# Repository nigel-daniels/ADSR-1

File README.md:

# Envelope Generator

This design is for an ADSR evvelope generator, it is based on the [Guru Gara Synth 3310 ADSR](https://gurugarasynth.com/products/3310-adsr-envelope-generator-eurorack-pcb-and-front-panel-for-diy-synth) AS3310 based envelope generator as this too uses the AS3310 and it's core. The design then adds in an LED indicator inspired by the [DIYSythMNL ADSR 3310](https://diysynthmnl.github.io/p/as3310-voltage-controlled-adsr/) and a gate trigger button of my own design.

## Calibration
The trim pot is used to fine tune the timing of the AS3310 attack phase, in the data sheet they use a 30K resistor but here we have a 16K resistor and a 20k trim pot. This adjusts the timing and is especially noticable on the attack. You probably want an oscilloscope for this although you can get close enough by ear.

> Nigel Daniels 2026
> https://bleepsnbloops.com
> Released under the CERN Open Hardware Licence Version 2 - Strongly Reciprocal

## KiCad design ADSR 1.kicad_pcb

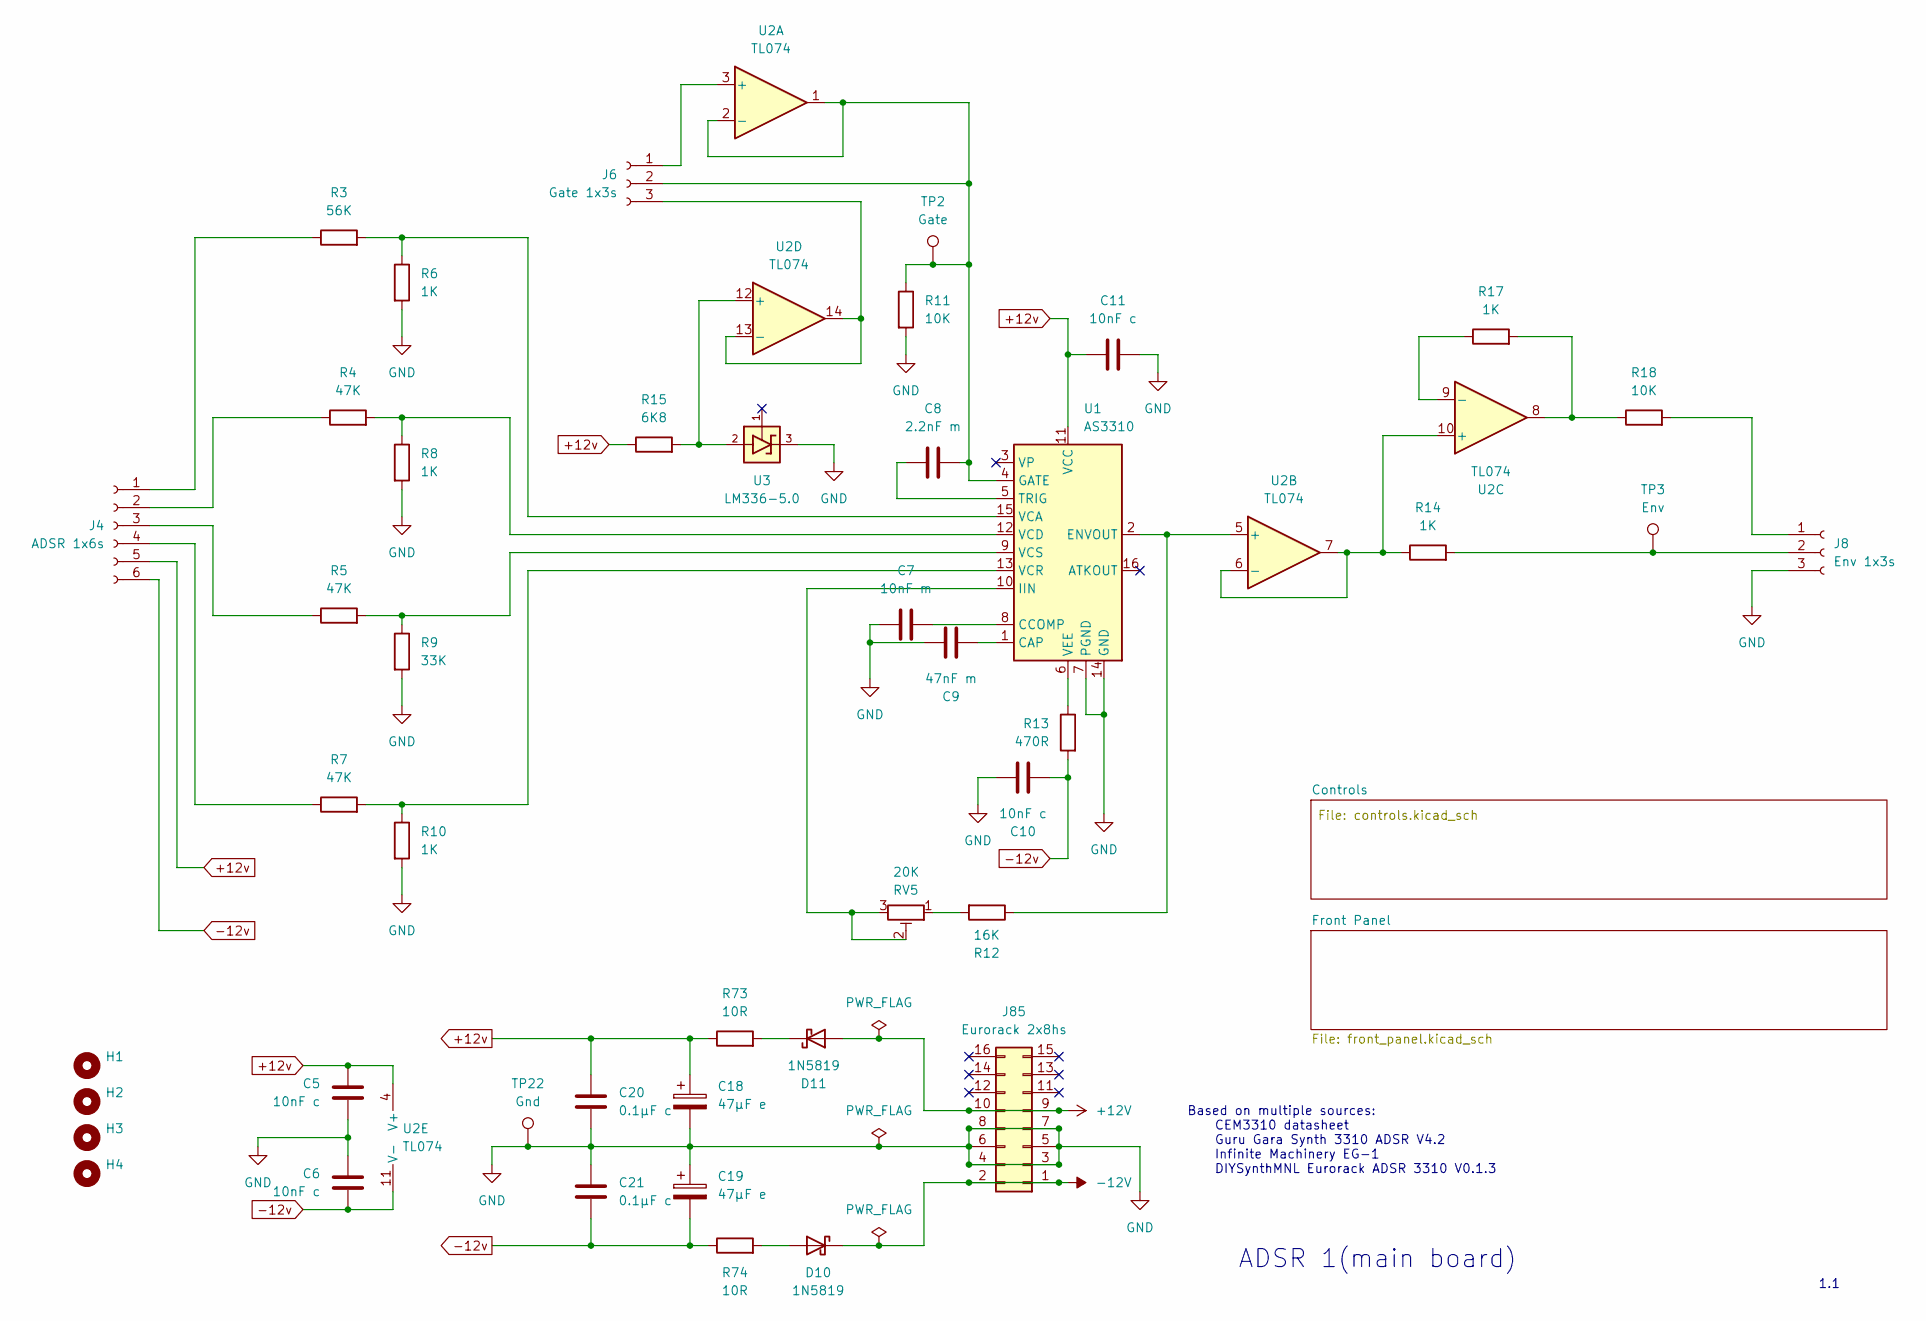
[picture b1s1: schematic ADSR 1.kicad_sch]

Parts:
C5, C6, C10, C11: 10nF c; C_Disc_D4.7mm_W2.5mm_P5.00mm
C7: 10nF m; C_Rect_L7.2mm_W2.5mm_P5.00mm
C8: 2.2nF m; C_Rect_L7.2mm_W2.5mm_P5.00mm
C9: 47nF m; C_Rect_L7.2mm_W2.5mm_P5.00mm
C18, C19: 47μF e; CP_Radial_D5.0mm_P2.50mm
C20, C21: 0.1μF c; C_Disc_D4.7mm_W2.5mm_P5.00mm
D10, D11: 1N5819; D_DO-41_SOD81_P10.16mm_Horizontal
H1, H2, H3, H4: MountingHole_2.7mm_M2.5
J4: ADSR 1x6s; PinSocket_1x06_P2.54mm_Vertical
J6: Gate 1x3s; PinSocket_1x03_P2.54mm_Vertical
J8: Env 1x3s; PinSocket_1x03_P2.54mm_Vertical
J85: Eurorack 2x8hs; IDC-Header_2x08_P2.54mm_Vertical
R3: 56K; R_Axial_DIN0204_L3.6mm_D1.6mm_P2.54mm_Vertical
R4, R5: 47K; R_Axial_DIN0204_L3.6mm_D1.6mm_P2.54mm_Vertical
R6, R8, R10, R17: 1K; R_Axial_DIN0204_L3.6mm_D1.6mm_P2.54mm_Vertical
R7: 47K; R_Axial_DIN0204_L3.6mm_D1.6mm_P7.62mm_Horizontal
R9: 33K; R_Axial_DIN0204_L3.6mm_D1.6mm_P2.54mm_Vertical
R11, R18: 10K; R_Axial_DIN0204_L3.6mm_D1.6mm_P7.62mm_Horizontal
R12: 16K; R_Axial_DIN0204_L3.6mm_D1.6mm_P7.62mm_Horizontal
R13: 470R; R_Axial_DIN0204_L3.6mm_D1.6mm_P7.62mm_Horizontal
R14: 1K; R_Axial_DIN0204_L3.6mm_D1.6mm_P7.62mm_Horizontal
R15: 6K8; R_Axial_DIN0204_L3.6mm_D1.6mm_P7.62mm_Horizontal
R73, R74: 10R; R_Axial_DIN0204_L3.6mm_D1.6mm_P2.54mm_Vertical
RV5: 20K; Potentiometer_Bourns_3296X_Horizontal
TP2: Gate; TestPoint_Loop_D2.50mm_Drill1.0mm
TP3: Env; TestPoint_Loop_D2.50mm_Drill1.0mm
TP22: Gnd; TestPoint_Loop_D2.50mm_Drill1.0mm
U1: AS3310; DIP-16_W7.62mm_Socket
U2: TL074; DIP-14_W7.62mm_Socket
U3: LM336-5.0; TO-92_Inline_Wide

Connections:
+12V: D11.2 (A), J85.9, J85.10
+12v: C5.2, C11.1, C18.1, C20.1, J4.5, R15.1, R73.1, U1.11 (VCC), U2.4 (V+)
-12V: D10.1 (K), J85.1, J85.2
-12v: C6.1, C10.2, C19.2, C21.2, J4.6, R13.2, R74.1, U2.11 (V-)
GND: C5.1, C6.2, C7.1, C9.1, C10.1, C11.2, C18.2, C19.1, C20.2, C21.1, J8.3, J85.3, J85.4, J85.5, J85.6, J85.7, J85.8, R6.2, R8.2, R9.2, R10.2, R11.2, TP22.1 (1_1), U1.7 (PGND), U1.14 (GND), U3.3; also elsewhere on the board
unnamed: D10.2 (A), R74.2
unnamed: D11.1 (K), R73.2
unnamed: J4.1, R3.1
unnamed: J4.2, R4.1
unnamed: J4.3, R5.1
unnamed: J4.4, R7.1
unnamed: J6.1, U2.3 (+)
unnamed: C8.2, J6.2, R11.1, TP2.1 (1_1), U1.4 (GATE), U2.1, U2.2 (-)
unnamed: J6.3, U2.13 (-), U2.14
unnamed: J8.1, R18.2
unnamed: J8.2, R14.2, TP3.1 (1_1)
unnamed: R12.2, RV5.1
unnamed: R17.2, R18.1, U2.8
unnamed: C9.2, U1.1 (CAP)
unnamed: C7.2, U1.8 (CCOMP)
unnamed: R12.1, U1.2 (ENVOUT), U2.5 (+)
unnamed: RV5.2, RV5.3, U1.10 (IIN)
unnamed: C8.1, U1.5 (TRIG)
unnamed: R3.2, R6.1, U1.15 (VCA)
unnamed: R4.2, R8.1, U1.12 (VCD)
unnamed: R7.2, R10.1, U1.13 (VCR)
unnamed: R5.2, R9.1, U1.9 (VCS)
unnamed: R13.1, U1.6 (VEE)
unnamed: R14.1, U2.6 (-), U2.7, U2.10 (+)
unnamed: R17.1, U2.9 (-)
unnamed: R15.2, U2.12 (+), U3.2

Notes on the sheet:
Based on multiple sources: CEM3310 datasheet Guru Gara Synth 3310 ADSR V4.2 Infinite Machinery EG-1 DIYSynthMNL Eurorack ADSR 3310 V0.1.3
1.1
ADSR 1(main board)

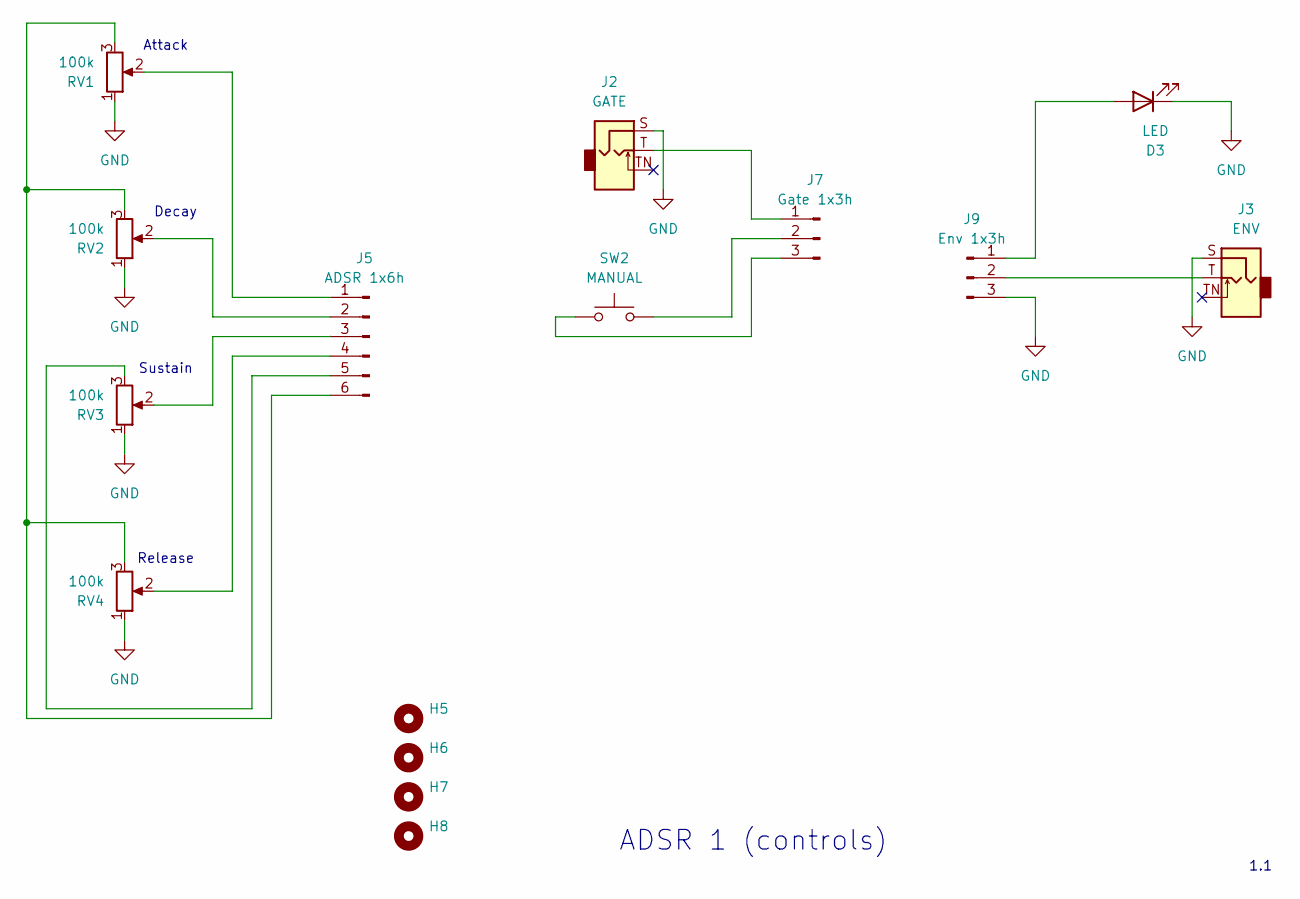
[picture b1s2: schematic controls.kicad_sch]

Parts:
D3: LED; LED_D3.0mm_FlatTop
H5, H6, H7, H8: MountingHole_2.7mm_M2.5
J2: GATE; Jack_3.5mm_QingPu_WQP-PJ398SM_Vertical_CircularHoles
J3: ENV; Jack_3.5mm_QingPu_WQP-PJ398SM_Vertical_CircularHoles
J5: ADSR 1x6h; PinHeader_1x06_P2.54mm_Vertical
J7: Gate 1x3h; PinHeader_1x03_P2.54mm_Vertical
J9: Env 1x3h; PinHeader_1x03_P2.54mm_Vertical
RV1, RV2, RV3, RV4: 100k; Potentiometer_Alps_RK09L_Single_Vertical
SW2: MANUAL; SW_Momentary_Push

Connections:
GND: D3.1 (K), J2.S, J3.S, J9.3, RV1.1, RV2.1, RV3.1, RV4.1; also elsewhere on the board
unnamed: D3.2 (A), J9.1
unnamed: J5.1, RV1.2
unnamed: J5.2, RV2.2
unnamed: J5.3, RV3.2
unnamed: J5.4, RV4.2
unnamed: J5.5, RV3.3
unnamed: J5.6, RV1.3, RV2.3, RV4.3
unnamed: J2.T, J7.1
unnamed: J7.2, SW2.2
unnamed: J7.3, SW2.1
unnamed: J3.T, J9.2

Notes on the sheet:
ADSR 1 (controls)
Sustain
1.1
Attack
Decay
Release

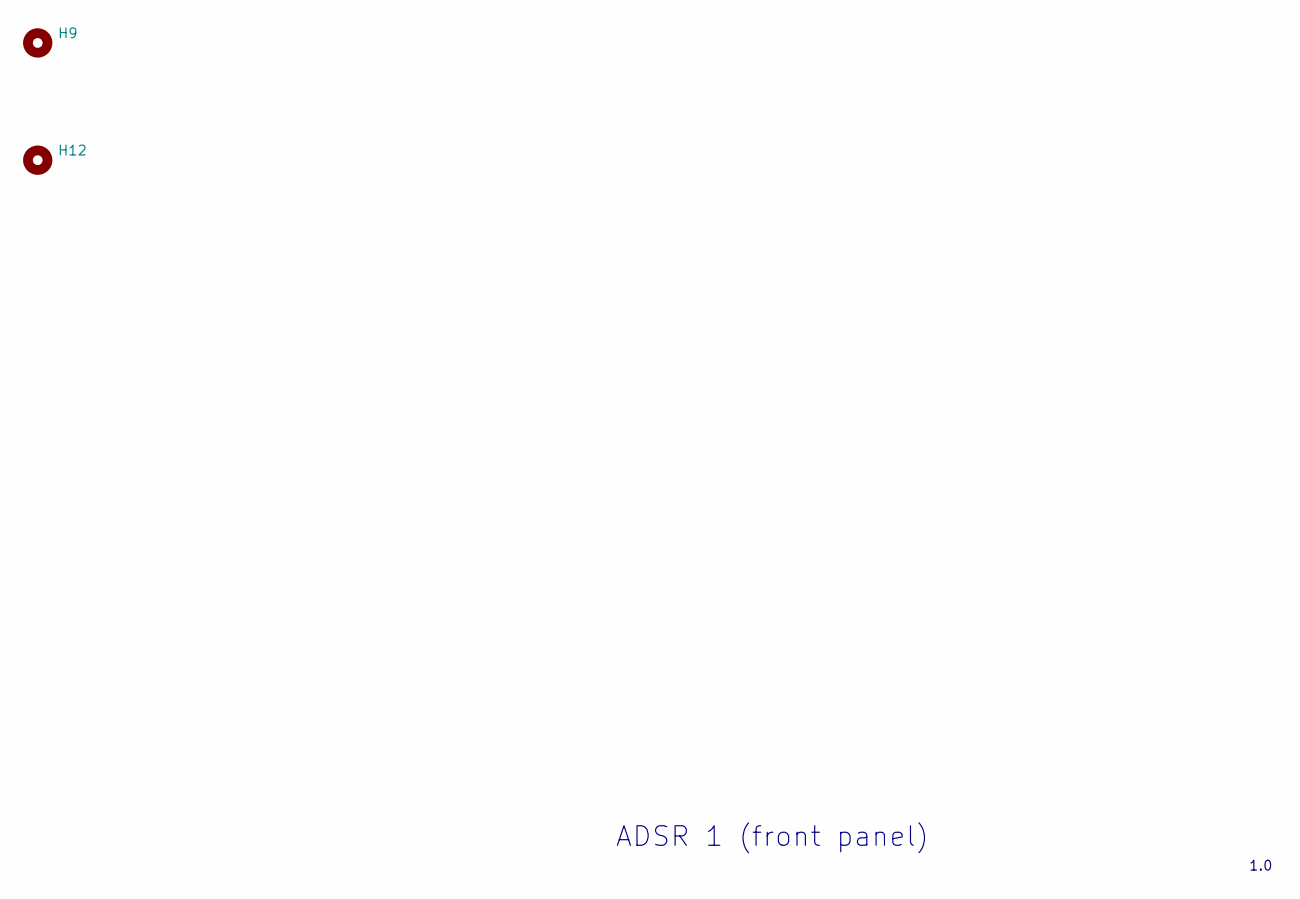
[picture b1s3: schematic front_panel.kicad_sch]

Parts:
H9, H12: MountingHole_3.2mm_M3

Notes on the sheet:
ADSR 1 (front panel)
1.0

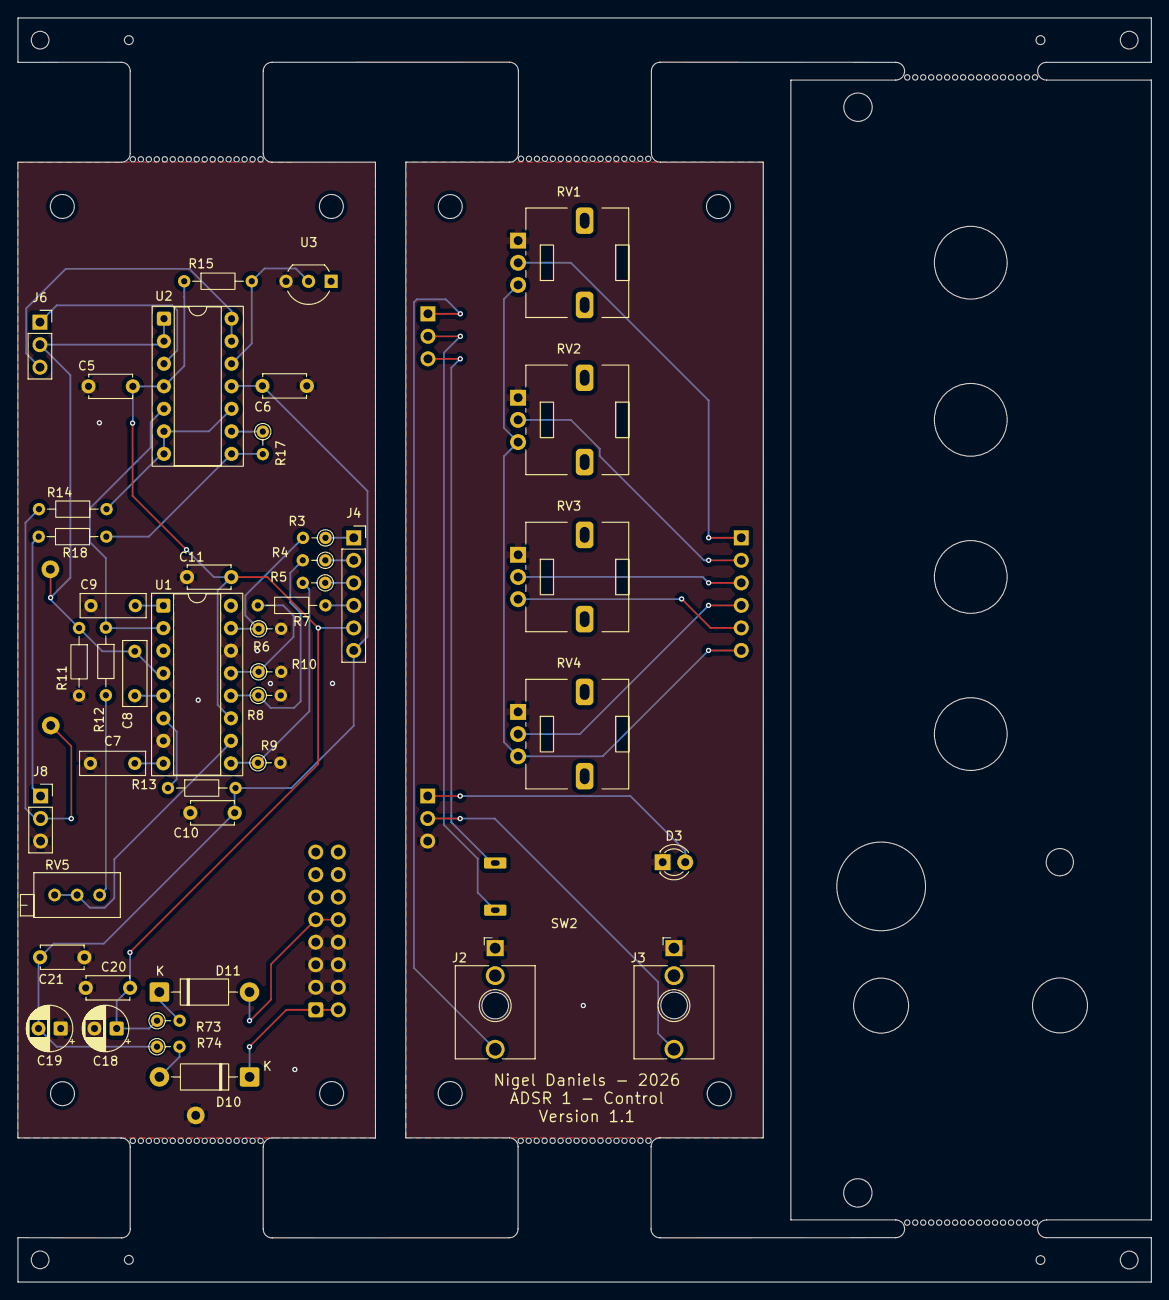
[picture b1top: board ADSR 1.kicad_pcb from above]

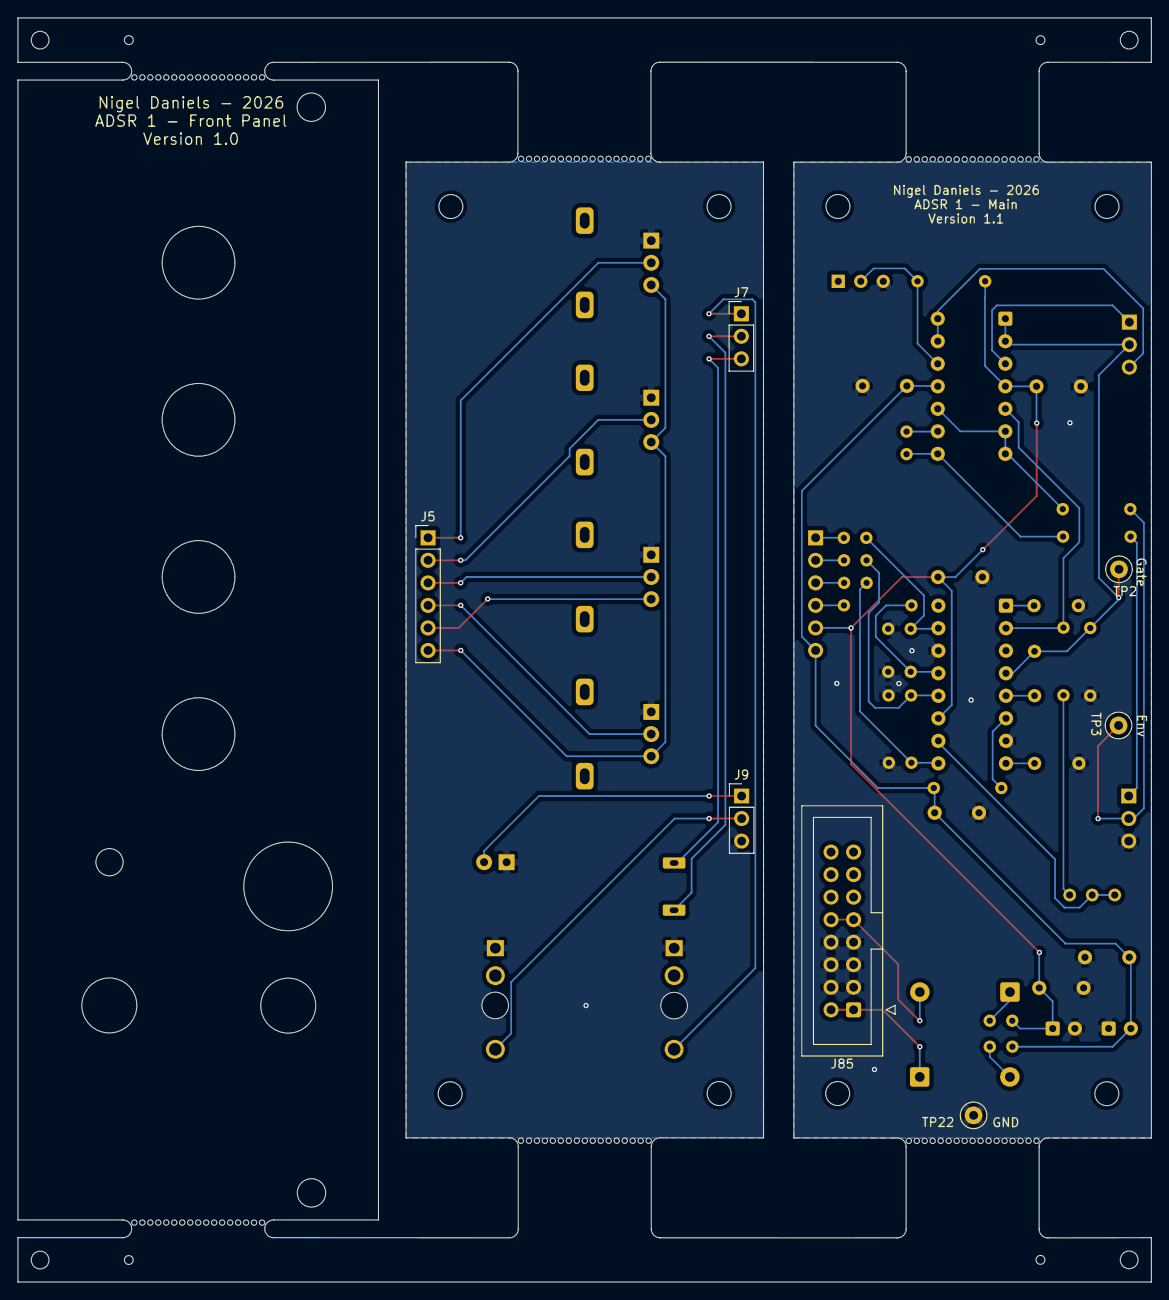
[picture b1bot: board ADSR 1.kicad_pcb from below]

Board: 2 copper layers, 127.8 x 142.5 mm, 62 parts (7 on the bottom side), 42 nets.
